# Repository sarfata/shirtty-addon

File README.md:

# shIRtty

A CircuitPython compatible, SAMD21 shitty addon with IR transmit/receive and RGB
LED.

## Bugs / Issues on v1.

**IMPORTANT** To make things more shitty the SAO header is upside down on the
badge. You will need a shitty inverser (included in this repo) or to put the
addon upside down. 

This is the pinout when looking at the face of the badge. Note that VCC is
bottom right (bottom left if you are looking at the connector).

### TODOs

- [ ] the SAO connector is upside down
- [ ] we need more capacitance on the +3V line otherwise we brown out when
    transmitting IR
- [ ] replace the very unreliable PCB usb connector by a micro usb connector
- [ ] make the reset button smaller so we can actually fit a SMD 6 pin SAO
    shrouded connector
- [ ] expose some GPIOs? 

## Micropython variant

### Build

Look at the readme in ports/atmel-samd.

```
# needed so gettext/msgfmt is available during build
export PATH="/usr/local/opt/gettext/bin:$PATH"

git clone git@github.com:adafruit/circuitpython.git
git submodule update --init --recursive
make -C mpy-cross

cd ports/atmel-samd

make BOARD=trinket_m0
(stopped there something funky going on where echo toto |xargs arm-none-eabi-gcc does not work)

```

## Bootloader

Some reference:

- https://forums.adafruit.com/viewtopic.php?f=57&t=142170&sid=a506885e77155bd9e062bbbab892efa3&start=15
- https://learn.adafruit.com/how-to-program-samd-bootloaders/itsybitsy-m0-m4-wiring

TODO:

- [x] Change the led configuration so they work on the RGB led we have on our board

### Build the bootloader

We only add two files from the adafruit version of the uf2 bootloader:

```
git clone git@github.com:adafruit/uf2-samdx1.git
```

`~/work/uf2-samdx1/boards/shirtty/board.mk`

```
CHIP_FAMILY = samd21
CHIP_VARIANT = SAMD21E18A
```

`uf2-samdx1/boards/shirtty/board_config.h`

```
#ifndef BOARD_CONFIG_H
#define BOARD_CONFIG_H

#define CRYSTALLESS 1

#define VENDOR_NAME "@sarfata"
#define PRODUCT_NAME "shIRtty"
#define VOLUME_LABEL "shIRtty"
#define INDEX_URL "https://github.com/sarfata/shirtty-addon"
#define BOARD_ID "shIRtty"

#define USB_VID 0x239A
#define USB_PID 0x001E

#define LED_PIN PIN_PA14

#endif
```

Then build with:

```
$ make BOARD=shirtty
```

I got an error at the end on a selfmain.c used for self update. #aintgottimeforthat - does not matter because the elf for the bootloader was built properly earlier.

### Using the Black Magic Probe

Connect:

- GND of the board to GND of BMP (use the SAO header)
- VCC of the board to VCC of BMP (use the SAO header)
- SWC/SWD/RST on the board to BMP (RST is optional - see below)

```
$ arm-none-eabi-gdb build/shirtty/bootloader-shirtty-v3.7.0-54-g63b4c6f.elf
(gdb) target extended-remote /dev/cu.usbmodem7AB17EC11

# If you need the black magic to provide power:
(gdb) monitor tpwr enable

(gdb) monitor swdp_scan
Target voltage: 3.3V
Available Targets:
No. Att Driver
 1      Atmel SAMD21E18A (rev D)
(gdb) attach 1

# if the bootloader is protected
(gdb) monitor unlock_bootprot

(gdb) load
(gdb) compare-sections

# if you want the new bootloader protected
(gdb) monitor lock_bootprot
```

Note: if you don't connect the RST line, you have to press reset after applying power, before running the `monitor` command. If the RST line is connected that is not needed.

### Unprotecting / Protecting the bootloader

First I had to update the firmware on my black magic probe (I had 1.6.1), I followed readme recommendations and installed daily build.

Version before:

    Black Magic Probe (Firmware 04d9749) (Hardware Version 3)

Upgrade with:

    sudo dfu-util -d 1d50:6018,:6017 -s 0x08002000:leave -D ~/Downloads/blackmagic-native.bin

Version after:

    Black Magic Probe (Firmware 04d9749) (Hardware Version 3)

Then the commands monitor unlock_bootprot becomes available.

Note: commands above do not work on the trinket m0 because the bootloader is protected. They should work on a fresh samd21e18 though.

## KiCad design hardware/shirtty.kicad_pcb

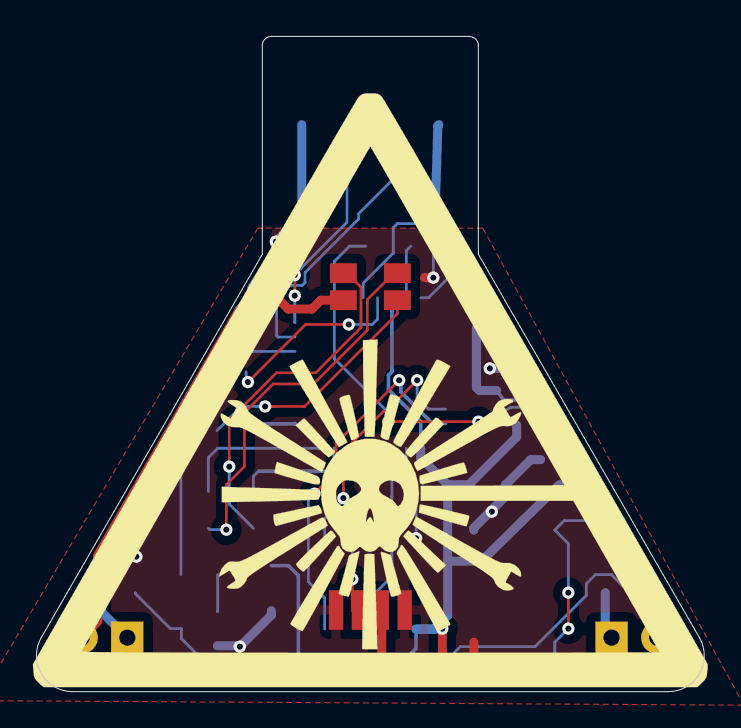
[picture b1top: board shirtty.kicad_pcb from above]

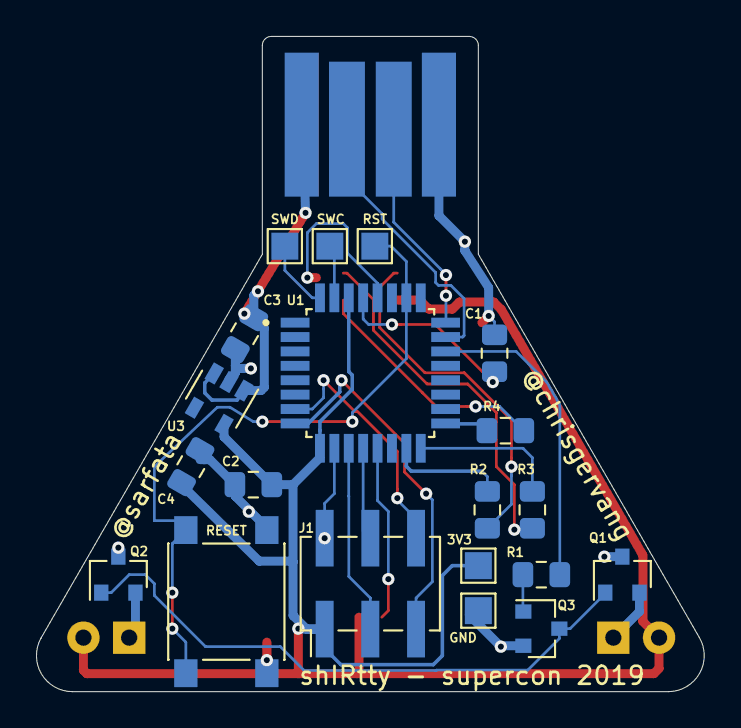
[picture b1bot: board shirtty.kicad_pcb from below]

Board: 2 copper layers, 37.1 x 36.4 mm, 25 parts (21 on the bottom side), 25 nets.

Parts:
3V3: Conn_01x01; TestPoint_Pad_1.5x1.5mm
C1, C2: 1uF; C_0805_2012Metric_Pad1.15x1.40mm_HandSolder
C3, C4: 10uF; C_0805_2012Metric_Pad1.15x1.40mm_HandSolder
D1, D2: LED; LED_D5.0mm
D3: LED_RGBA; LED_Avago_PLCC4_3.2x2.8mm_CW
GND: Conn_01x01; TestPoint_Pad_1.5x1.5mm
J1: Conn_02x03_Odd_Even; PinHeader_2x03_P2.54mm_Vertical_SMD
J2: USB_PCB; usb-PCB
Q1, Q2: Q_PNP_BEC; SOT-23
Q3: Q_NPN_BEC; SOT-23
R1, R2, R3, R4: 1k; R_0805_2012Metric_Pad1.15x1.40mm_HandSolder
RESET: SW_SPST; SW_Push_1P1T_NO_6x6mm_H9.5mm
RST: Conn_01x01; TestPoint_Pad_1.5x1.5mm
SWC: Conn_01x01; TestPoint_Pad_1.5x1.5mm
SWD: Conn_01x01; TestPoint_Pad_1.5x1.5mm
U1: ATSAMD21E18A-AF; QFP80P900X900X120-32N
U2: TSOP77438; TSOP774xx
U3: AP2112K-3.3; SOT-23-5

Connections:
+3V3: 3V3.1, C2.1, C4.1, D1.2, D2.2, D3.4, J1.1, U1.9, U1.30, U2.2, U3.5
/GPIO1_RXD_D3: J1.5, U1.8
/GPIO2_TXD_D4: J1.6, U1.7
/IRRX_D13: U1.13, U2.3
/IRTX: R1.2, U1.22
/RESET: RESET.2, RST.1, U1.26
/RGB_B: R4.2, U1.17
/RGB_G: R3.2, U1.16
/RGB_R: R2.2, U1.15
/SCL_D2: J1.4, U1.12
/SDA_D0: J1.3, U1.11
/SWCLK: SWC.1, U1.31
/SWDIO: SWD.1, U1.32
/USB_DM: J2.2, U1.23
/USB_DP: J2.3, U1.24
/VBUS: C3.1, J2.1, U3.1, U3.3
GND: C1.2, C2.2, C3.2, C4.2, GND.1, J1.2, J2.4, Q1.3, Q2.3, Q3.2, RESET.1, U1.10, U1.28, U2.1, U2.4, U3.2
unnamed: C1.1, U1.29
unnamed: D1.1, Q1.2
unnamed: D2.1, Q2.2
unnamed: D3.1, R2.1
unnamed: D3.2, R3.1
unnamed: D3.3, R4.1
unnamed: Q1.1, Q2.1, Q3.3
unnamed: Q3.1, R1.1

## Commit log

2019-10-29 initial commit of hardware
2019-11-06 add shitty-inverser
2019-11-09 feature: route inverser so it works without metallized hole
2019-11-09 code v0
2019-11-09 readme v0
2019-11-16 Updating Friday night fixes. Power remote to turn off!
2019-11-16 add irremote libbrary
2019-11-16 Adding a firmware readme!
2019-11-16 color library!
2019-11-16 doc: add pinout info
2019-11-16 Adding a WIP pulse library
2019-11-16 Finishing codes and pulses library
2019-11-16 Finished a ShittyIr module
2019-11-16 Add lambda signal matcher ability
2019-11-16 Adding neopixels and making files smaller
2019-11-16 ShittyColor class
2019-11-17 introduce modes
2019-11-17 Add "react_to" library
2019-11-17 Combine IR Files
2019-11-18 initialize known problems list
2019-11-18 notify badge when we get a hit
2019-12-12 doc: add some photos of shirtty
2020-04-24 fix the shitty todo list
